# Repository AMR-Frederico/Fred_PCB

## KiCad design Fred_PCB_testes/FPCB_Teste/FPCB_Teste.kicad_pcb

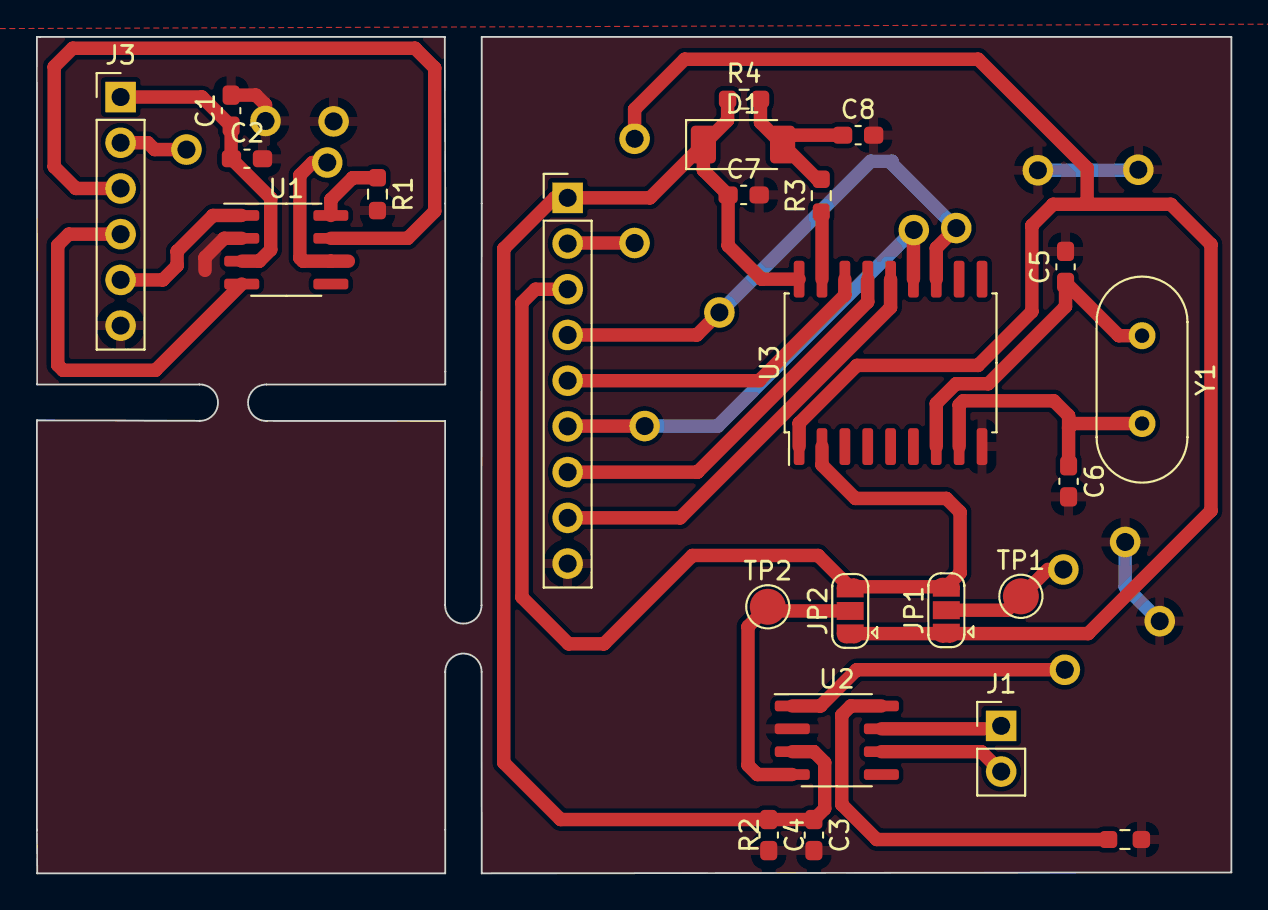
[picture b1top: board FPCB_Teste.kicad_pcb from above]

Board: 2 copper layers, 66.4 x 46.5 mm, 24 parts (0 on the bottom side), 23 nets.

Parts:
C1, C3, C7: 0,1uF; C_0603_1608Metric_Pad1.08x0.95mm_HandSolder
C2, C4: 2,2uF; C_0603_1608Metric_Pad1.08x0.95mm_HandSolder
C5, C6: 22pF; C_0603_1608Metric_Pad1.08x0.95mm_HandSolder
C8: C; C_0603_1608Metric_Pad1.08x0.95mm_HandSolder
D1: D; D_SOD-128
J1: Conn_01x02; PinHeader_1x02_P2.54mm_Vertical
J2: Conn_01x09; PinHeader_1x09_P2.54mm_Vertical
J3: Conn_01x06; PinHeader_1x06_P2.54mm_Vertical
JP1, JP2: SolderJumper_3_Open; SolderJumper-3_P1.3mm_Open_RoundedPad1.0x1.5mm
R1, R2: Rs; R_0603_1608Metric_Pad0.98x0.95mm_HandSolder
R3, R4: R; R_0603_1608Metric_Pad0.98x0.95mm_HandSolder
TP1, TP2: TestPoint; TestPoint_Pad_D2.0mm
U1, U2: SN65HVD230; SOIC-8_3.9x4.9mm_P1.27mm
U3: MCP2515-xSO; SOIC-18W_7.5x11.6mm_P1.27mm
Y1: Crystal; Crystal_HC49-4H_Vertical

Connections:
3,3v: C1.1, C2.1, C3.1, C4.1, C7.1, D1.1 (K), J2.1, J3.1, R4.1, U1.3 (VCC), U2.3 (VCC), U3.18 (VDD)
/MCP2515/GPIO9(MISO): J2.7, U3.15 (SO)
/MCP2515/GPIO10(MOSI): J2.8, U3.14 (SI)
/MCP2515/GPIO11(SCLK): J2.6, U3.13 (SCK)
/MCP2515/GPIO22: J2.5, U3.16 (~CS)
/MCP2515/GPIO26: J2.4, U3.12 (~INT)
/MCP2515/RXCAN: J2.3, JP1.3 (B), JP2.3 (B), U3.2 (RXCAN)
/MCP2515/TXCAN: J2.2, JP1.1 (A), JP2.1 (A), U3.1 (TXCAN)
/SN65HVD230/CANH: J3.3, U1.7 (CANH)
/SN65HVD230/CANL: J3.2, U1.6 (CANL)
/SN65HVD230/D: J3.5, U1.1 (D)
/SN65HVD230/R: J3.4, U1.4 (R)
/SN65HVD231_RASP/CANH: J1.1, U2.7 (CANH)
/SN65HVD231_RASP/CANL: J1.2, U2.6 (CANL)
/SN65HVD231_RASP/D: JP1.2 (C), TP1.1, U2.1 (D)
/SN65HVD231_RASP/R: JP2.2 (C), TP2.1, U2.4 (R)
GND: C1.2, C2.2, C3.2, C4.2, C5.2, C6.2, C7.2, C8.2, J2.9, J3.6, R1.2, R2.2, U1.2 (GND), U2.2 (GND), U3.9 (VSS)
unnamed: C8.1, D1.2 (A), R3.2, R4.2
unnamed: R1.1, U1.8 (Rs)
unnamed: R2.1, U2.8 (Rs)
unnamed: C6.1, U3.8 (OSC1), Y1.2
unnamed: C5.1, U3.7 (OSC2), Y1.1
unnamed: R3.1, U3.17 (~RESET)

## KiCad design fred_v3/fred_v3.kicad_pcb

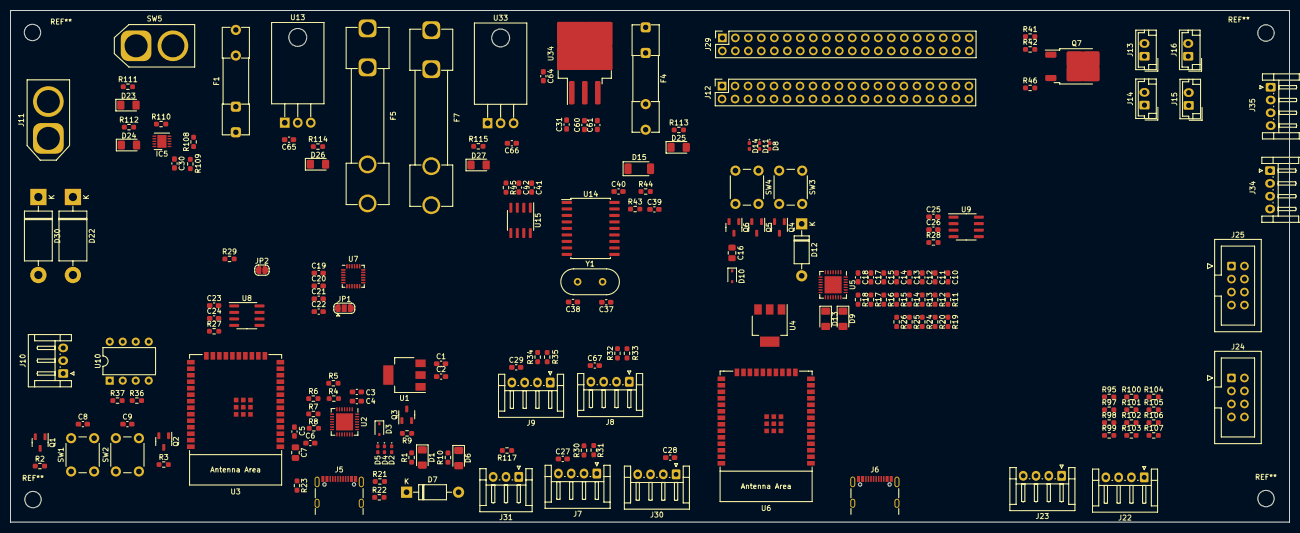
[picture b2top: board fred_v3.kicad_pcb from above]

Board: 2 copper layers, 250.0 x 100.0 mm, 185 parts (0 on the bottom side), 133 nets, no tracks yet.

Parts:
C1, C2, C10, C13, C64: 22uF; C_0603_1608Metric_Pad1.08x0.95mm_HandSolder
C3, C11: 4.7uF; C_0603_1608Metric_Pad1.08x0.95mm_HandSolder
C4, C5, C6, C8, C9, C12, C14, C15, C17, C18: 0.1uF; C_0603_1608Metric_Pad1.08x0.95mm_HandSolder
C7, C16: 22uF; C_0805_2012Metric_Pad1.18x1.45mm_HandSolder
C19: 2,2nF; C_0603_1608Metric_Pad1.08x0.95mm_HandSolder
C20: 2.2uF; C_0603_1608Metric_Pad1.08x0.95mm_HandSolder
C21, C23, C25, C40, C41, C65, C66: 0,1uF; C_0603_1608Metric_Pad1.08x0.95mm_HandSolder
C22: 10nF; C_0603_1608Metric_Pad1.08x0.95mm_HandSolder
C24, C26, C42, C60, C61: 2,2uF; C_0603_1608Metric_Pad1.08x0.95mm_HandSolder
C27, C28, C29, C67: 100nF; C_0603_1608Metric_Pad1.08x0.95mm_HandSolder
C30, C39: C; C_0603_1608Metric_Pad1.08x0.95mm_HandSolder
C31: 10uF; C_0603_1608Metric_Pad1.08x0.95mm_HandSolder
C37, C38: 22pF; C_0603_1608Metric_Pad1.08x0.95mm_HandSolder
D1, D6, D9, D13: LED; LED_1206_3216Metric_Pad1.42x1.75mm_HandSolder
D2, D4, D5, D8, D11, D14: GG0402055R042P; D_0402_1005Metric_Pad0.77x0.64mm_HandSolder
D3, D10: BAT760-7; D_SOD-323
D7, D12: 1N4007; D_DO-41_SOD81_P10.16mm_Horizontal
D15: D; D_SOD-128
D22, D30: DIODE 4AMP; D_DO-201AD_P15.24mm_Horizontal
D23: BLC; LED_1206_3216Metric_Pad1.42x1.75mm_HandSolder
D24: BLF; LED_1206_3216Metric_Pad1.42x1.75mm_HandSolder
D25: RSF; LED_1206_3216Metric_Pad1.42x1.75mm_HandSolder
D26: E1F; LED_1206_3216Metric_Pad1.42x1.75mm_HandSolder
D27: E2F; LED_1206_3216Metric_Pad1.42x1.75mm_HandSolder
F1: Fuse 6Amp; Fuseholder_Clip-5x20mm_Littelfuse_111_Inline_P20.00x5.00mm_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
F4: Fuse 4Amp; Fuseholder_Clip-5x20mm_Littelfuse_111_Inline_P20.00x5.00mm_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
F5, F7: Fuse 1Amp; Fuseholder_Clip-6.3x32mm_Littelfuse_102_Inline_P34.21x7.62m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
IC5: PAC1921-1-AIA-TR; WDFN-10-1EP_3x3mm_P0.5mm_EP1.8x2.5mm
J5, J6: USB_C_Receptacle_USB2.0; USB_C_Receptacle_GCT_USB4105-xx-A_16P_TopMnt_Horizontal
J7, J8, J9, J22, J23, J30, J34, J35: Conn_01x04; JST_EH_S4B-EH_1x04_P2.50mm_Horizontal
J10, J31: Conn_01x03; JST_EH_S3B-EH_1x03_P2.50mm_Horizontal
J11: Conn_01x02; AMASS_XT60-M_1x02_P7.20mm_Vertical
J12, J29: Conn_02x20_Odd_Even; PinSocket_2x20_P2.54mm_Vertical
J13: FAN1; JST_EH_B2B-EH-A_1x02_P2.50mm_Vertical
J14: FAN2; JST_EH_B2B-EH-A_1x02_P2.50mm_Vertical
J15: FAN3; JST_EH_B2B-EH-A_1x02_P2.50mm_Vertical
J16: FAN4; JST_EH_B2B-EH-A_1x02_P2.50mm_Vertical
J24, J25: Conn_02x04_Odd_Even; IDC-Header_2x04_P2.54mm_Vertical
JP1: SolderJumper_3_Open; SolderJumper-3_P1.3mm_Open_RoundedPad1.0x1.5mm
JP2: SolderJumper_2_Open; SolderJumper-2_P1.3mm_Open_RoundedPad1.0x1.5mm
Q1, Q2, Q5, Q6: SS8050-G; SOT-23-3
Q3, Q4: Q_PMOS_GSD; SOT-23-3
Q7: NMOS; TO-252-2
R1, R6, R15, R18: 2k; R_0603_1608Metric_Pad0.98x0.95mm_HandSolder
R2, R3, R7, R8, R13, R14, R19, R20, R46, R98, R101, R104, R107: 10k; R_0603_1608Metric_Pad0.98x0.95mm_HandSolder
R4, R16: 22.1k; R_0603_1608Metric_Pad0.98x0.95mm_HandSolder
R5, R17: 47.5k; R_0603_1608Metric_Pad0.98x0.95mm_HandSolder
R9, R11: 1K; R_0603_1608Metric_Pad0.98x0.95mm_HandSolder
R10, R12: 1k; R_0603_1608Metric_Pad0.98x0.95mm_HandSolder
R21, R24, R41, R42, R43, R44, R109, R110: R; R_0603_1608Metric_Pad0.98x0.95mm_HandSolder
R22, R23, R25, R26: 5,11k; R_0603_1608Metric_Pad0.98x0.95mm_HandSolder
R27, R28, R45: Rs; R_0603_1608Metric_Pad0.98x0.95mm_HandSolder
R29: 120; R_0603_1608Metric_Pad0.98x0.95mm_HandSolder
R30, R31, R32, R33, R34, R35: 10K; R_0603_1608Metric_Pad0.98x0.95mm_HandSolder
R36: 3,5k; R_0603_1608Metric_Pad0.98x0.95mm_HandSolder
R37: 6,5k; R_0603_1608Metric_Pad0.98x0.95mm_HandSolder
R95, R99, R102, R105: 4,7k; R_0603_1608Metric_Pad0.98x0.95mm_HandSolder
R97, R100, R103, R106: 2,2k; R_0603_1608Metric_Pad0.98x0.95mm_HandSolder
R108: R_Shunt; R_0603_1608Metric_Pad0.98x0.95mm_HandSolder
R111, R112, R113, R114, R115: 330; R_0603_1608Metric_Pad0.98x0.95mm_HandSolder
R117: Pull_Up Hall (Pode não ser necessário); R_0603_1608Metric_Pad0.98x0.95mm_HandSolder
SW1, SW2, SW3, SW4: SW_Push; SW_PUSH_6mm
SW5: SW_DIP_x01; AMASS_XT60-M_1x02_P7.20mm_Vertical
U1, U4: AMS1117-3.3; SOT-223-3_TabPin2
U2, U5: CP2102N-Axx-xQFN28; QFN-28-1EP_5x5mm_P0.5mm_EP3.35x3.35mm
U3, U6: ESP32-WROOM-E; ESP32-WROOM-32E
U7: MPU-6050; InvenSense_QFN-24_4x4mm_P0.5mm
U8, U9, U15: SN65HVD230; SOIC-8_3.9x4.9mm_P1.27mm
U10: AD8001AN; DIP-8_W7.62mm
U13, U33: L7805; TO-220-3_Horizontal_TabDown
U14: MCP2515-xSO; SOIC-18W_7.5x11.6mm_P1.27mm
U34: AZ1084-5.0; TO-263-3_TabPin2
Y1: Crystal; Crystal_HC49-4H_Vertical

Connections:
3,3V: C2.1, C3.1, C4.1, C6.1, C7.1, C20.1, C22.2, C23.1, C24.1, JP1.3 (B), R6.1, R8.1, U1.2 (VO), U2.6 (VDD), U2.7 (VREGIN), U3.2 (3V3), U7.8 (VLOGIC), U7.13 (VDD), U8.3 (VCC)
3,3v: C25.1, C26.1, C40.1, C41.1, C42.1, D15.1 (K), J12.1, J12.17, J29.1, J29.17, J34.4, J35.4, R41.1, R42.1, R44.1, R109.1, U9.3 (VCC), U14.18 (VDD), U15.3 (VCC)
3.3V: C11.1, C12.1, C13.1, C15.1, C16.1, R18.1, R20.1, U4.2 (VO), U5.6 (VDD), U5.7 (VREGIN), U6.2 (3V3)
5V: F4.2, IC5.7 (RESERVED), J12.2, J12.4, J29.2, J29.4, R113.1
5V_1: C65.1, F5.1, U13.3 (OUT)
5V_2: C66.1, F7.1, U33.3 (OUT)
5V_USB: C1.1, C10.1, D3.1 (K), D7.1 (K), D10.1 (K), D12.1 (K), Q3.1 (G), Q4.1 (G), R1.1, R4.1, R9.2, R11.2, R15.1, R16.1, U1.3 (VI), U4.3 (VI)
12V_IN: F1.2, SW5.2
/Lógica/CANH: R29.1, U8.7 (CANH), U9.7 (CANH), U15.7 (CANH)
/Lógica/CANL: JP2.1 (A), U8.6 (CANL), U9.6 (CANL), U15.6 (CANL)
/Lógica/LED_LVL_SHIFTER/EXT_5V: J10.2, R37.1, U10.7 (V+)
/Lógica/LED_LVL_SHIFTER/LED_OUT: J10.1, U10.6
A_LEFT: J22.3, R95.1, R97.1
A_RIGHT: J23.3, R102.1, R103.1
B_LEFT: J22.4, R99.1, R100.1
B_RIGHT: J23.4, R105.1, R106.1
Current_Sense1: J24.2, J25.2, U6.24 (ADC2_CH2/GPIO2)
Current_Sense2: J24.4, J25.4, U6.26 (ADC2_CH0/GPIO4)
D+: D5.2 (A2), D14.2 (A2), J5.A6 (D+), J5.B6 (D+), J6.A6 (D+), J6.B6 (D+), U2.4 (D+), U5.4 (D+)
D-: D4.2 (A2), D11.2 (A2), J5.A7 (D-), J5.B7 (D-), J6.A7 (D-), J6.B7 (D-), U2.5 (D-), U5.5 (D-)
DTR: Q2.2 (C), Q6.2 (C), R2.1, R13.1, U2.28 (~DTR), U5.28 (~DTR)
ECHO1: J7.2, R30.1
ECHO2: J8.2, R32.1
ECHO3: J9.2, R34.1
EN: C5.1, C8.2, C14.1, C17.2, Q1.2 (C), Q5.2 (C), R8.2, R20.2, SW1.2, SW3.2, U3.3 (EN/CHIP_PU), U6.3 (EN/CHIP_PU)
EXT_5V: C27.1, C28.1, C29.1, C67.1, F5.2, F7.2, J7.4, J8.4, J9.4, J22.1, J23.1, J30.1, J31.1, Q3.3 (D), Q4.3 (D), R95.2, R99.2, R102.2, R105.2, R114.1, R115.1, R117.1
GND: C1.2, C2.2, C3.2, C4.2, C5.2, C6.2, C7.2, C8.1, C9.1, C10.2, C11.2, C12.2, C13.2, C14.2, C15.2, C16.2, C17.1, C18.1, C19.2, C20.2, C21.2, C22.1, C23.2, C24.2, C25.2, C26.2, C27.2, C28.2, C29.2, C30.2, C31.2, C37.2, C38.2, C39.2, C40.2, C41.2, C42.2, C60.2, C61.2, C64.2, C65.2, C66.2, C67.2, D1.1 (K), D2.1 (A1), D4.1 (A1), D5.1 (A1), D6.1 (K), D8.1 (A1), D9.1 (K), D11.1 (A1), D13.1 (K), D14.1 (A1), D22.2 (A), D23.1 (K), D24.1 (K), D25.1 (K), D26.1 (K), D27.1 (K), D30.2 (A), IC5.5 (GND), IC5.11 (EP), J5.A1 (GND), J5.A12 (GND), J5.B1 (GND), J5.B12 (GND), J6.A1 (GND), J6.A12 (GND), J6.B1 (GND), J6.B12 (GND), J7.1, J8.1, J9.1, J10.3, J12.6, J12.9, J12.14, J12.20, J12.25, J12.30, J12.34, J12.39, J13.2, J14.2, J15.2, J16.2, J22.2, J23.2, J29.6, J29.9, J29.14, J29.20, J29.25, J29.30, J29.34, J29.39, J30.2, J31.2, J34.3, J35.3, JP1.1 (A), R5.2, R7.2, R9.1, R11.1, R17.2, R19.2, R21.2, R22.2, R23.2, R24.2, R25.2, R26.2, R27.2, R28.2, R31.1, R33.1, R35.1, R36.2, R45.2, R46.1, R98.1, R101.1, R104.1, R107.1, R110.2, SW1.1, SW2.1, SW3.1, SW4.1, U1.1 (GND), U2.3 (GND), U2.29 (GND), U3.1 (GND), U3.15 (GND), U3.38 (GND), U3.39 (GND_THERMAL), U4.1 (GND), U5.3 (GND), U5.29 (GND), U6.1 (GND), U6.15 (GND), U6.38 (GND), U6.39 (GND_THERMAL), U7.1 (CLKIN), U7.11 (FSYNC), U7.18 (GND), U8.2 (GND), U9.2 (GND), U10.4 (V-), U13.2 (GND), U14.9 (VSS), U15.2 (GND), U33.2 (GND), U34.1 (GND)
GPIO0(ID_SD): J12.27, J29.27
GPIO1(ID_SC): J12.28, J29.28
GPIO2(SDA): IC5.9 (SM_DATA), J12.3, J29.3, J34.2, J35.2, R42.2
GPIO3(SCL): IC5.10 (SM_CLK), J12.5, J29.5, J34.1, J35.1, R41.2
GPIO4(GPCLK0): J12.7, J29.7
GPIO5: J12.29, J29.29
GPIO6: IC5.8 (~READ/INT), J12.31, J29.31
GPIO7(CE1): J12.26, J29.26
GPIO8(CE0): J12.24, J29.24
GPIO9(MISO): J12.21, J29.21, U14.15 (SO)
GPIO10(MOSI): J12.19, J29.19, U14.14 (SI)
GPIO11(SCLK): J12.23, J29.23, U14.13 (SCK)
GPIO12(PWM0): J12.32, J29.32, Q7.2 (G), R46.2
GPIO13(PWM1): J12.33, J29.33
GPIO14(TXD): J12.8, J29.8
GPIO15(RXD): J12.10, J29.10
GPIO16: J12.36, J29.36
GPIO17: J12.11, J29.11
GPIO18(PCM_CLK): J12.12, J29.12
GPIO19(PCM_FS): J12.35, J29.35
GPIO20(PCM_DIN): J12.38, J29.38
GPIO21(PCM_DOUT): J12.40, J29.40
GPIO22: J12.15, J29.15, U14.16 (~CS)
GPIO23: J12.16, J29.16
GPIO24: J12.18, J29.18
GPIO25: J12.22, J29.22
GPIO26: J12.37, J29.37, U14.12 (~INT)
GPIO27: J12.13, J29.13
INA_M1_FRONT: J24.1, J25.1, U6.8 (32K_XP/GPIO32/ADC1_CH4)
INA_M2_FRONT: J24.7, J25.7, U6.28 (GPIO17)
INB_M1_FRONT: J24.3, J25.3, U6.29 (GPIO5)
INB_M2_FRONT: J24.6, J25.6, U6.30 (GPIO18)
INT: U3.30 (GPIO18), U7.12 (INT)
IO0: C9.2, C18.2, Q2.3 (E), Q6.3 (E), SW2.2, SW4.2, U3.25 (GPIO0/BOOT/ADC2_CH1), U6.25 (GPIO0/BOOT/ADC2_CH1)
IO5: U3.29 (GPIO5), U10.3 (+)
IO12: J9.3, U3.14 (MTDI/GPIO12/ADC2_CH5)
IO13: U3.16 (MTCK/GPIO13/ADC2_CH4), U6.16 (MTCK/GPIO13/ADC2_CH4)
IO14: U3.13 (MTMS/GPIO14/ADC2_CH6), U6.13 (MTMS/GPIO14/ADC2_CH6)
IO16: U3.27 (GPIO16), U8.4 (R), U9.4 (R)
IO17: U3.28 (GPIO17), U8.1 (D), U9.1 (D)
IO21: J30.4, U3.33 (GPIO21), U7.24 (SDA)
IO25: J7.3, U3.10 (DAC_1/ADC2_CH8/GPIO25)
IO27: J8.3, U3.12 (ADC2_CH7/GPIO27)
IO32: R34.2, R35.2, R97.2, R98.2, U3.8 (32K_XP/GPIO32/ADC1_CH4)
IO33: R100.2, R101.2, U3.9 (32K_XN/GPIO33/ADC1_CH5), U6.9 (32K_XN/GPIO33/ADC1_CH5)
IO34: R32.2, R33.2, R103.2, R104.2, U3.6 (GPIO34/ADC1_CH6), U6.6 (GPIO34/ADC1_CH6)
IO35: R106.2, R107.2, U3.7 (GPIO35/ADC1_CH7), U6.7 (GPIO35/ADC1_CH7)
IO36: R30.2, R31.2, U3.4 (SENSOR_VP/GPIO36/ADC1_CH0), U6.4 (SENSOR_VP/GPIO36/ADC1_CH0)
IO39: J31.3, R117.2, U3.5 (SENSOR_VN/GPIO39/ADC1_CH3), U6.5 (SENSOR_VN/GPIO39/ADC1_CH3)
unnamed: D1.2 (A), R1.2
unnamed: D6.2 (A), R10.2
unnamed: D7.2 (A), Q3.2 (S), R10.1
unnamed: D9.2 (A), R12.2
unnamed: D12.2 (A), Q4.2 (S), R12.1
unnamed: D13.2 (A), R15.2
unnamed: C39.1, D15.2 (A), R43.2, R44.2
unnamed: D22.1 (K), D30.1 (K), J11.1
unnamed: D23.2 (A), R111.2
unnamed: D24.2 (A), R112.2
unnamed: D25.2 (A), R113.2
unnamed: D26.2 (A), R114.2
unnamed: D27.2 (A), R115.2
unnamed: IC5.6 (ADDR_SEL), R110.1
unnamed: F1.1, IC5.2 (SENSE+), R108.1
unnamed: C30.1, IC5.1 (VDD), R109.2
unnamed: J5.A5 (CC1), R23.1
unnamed: J5.B5 (CC2), R22.1
unnamed: J5.S1 (SHIELD), R21.1
unnamed: J6.A5 (CC1), R26.1
unnamed: J6.B5 (CC2), R25.1
unnamed: J6.S1 (SHIELD), R24.1
unnamed: J11.2, R111.1, SW5.1
unnamed: J13.1, J14.1, J15.1, J16.1, Q7.3 (S)
unnamed: JP1.2 (C), U7.9 (AD0)
unnamed: JP2.2 (B), R29.2
unnamed: Q1.1 (B), R2.2
unnamed: Q2.1 (B), R3.2
unnamed: Q5.1 (B), R13.2
unnamed: Q6.1 (B), R14.2
unnamed: R6.2, U2.9 (~RST)
unnamed: R7.1, U2.11 (~SUSPEND)
unnamed: R18.2, U5.9 (~RST)
unnamed: R19.1, U5.11 (~SUSPEND)
unnamed: C19.1, U7.20 (CPOUT)
unnamed: C21.1, U7.10 (REGOUT)
unnamed: R27.1, U8.8 (Rs)
unnamed: R28.1, U9.8 (Rs)
unnamed: R36.1, R37.2, U10.2 (-)
unnamed: C37.1, U14.8 (OSC1), Y1.2
unnamed: C38.1, U14.7 (OSC2), Y1.1
unnamed: R43.1, U14.17 (~RESET)
unnamed: R45.1, U15.8 (Rs)
unnamed: C64.1, F4.1, U34.2 (VO)
PWM_M1_FRONT: J24.5, J25.5, U6.27 (GPIO16)
PWM_M2_FRONT: J24.8, J25.8, U6.31 (GPIO19)
RTS: Q1.3 (E), Q5.3 (E), R3.1, R14.1, U2.24 (~RTS), U5.24 (~RTS)
RXCAN: U14.2 (RXCAN), U15.4 (R)
RXD: U2.25 (RXD), U5.25 (RXD)
RXD0: U3.35 (U0TXD/GPIO1), U6.35 (U0TXD/GPIO1)
SCL: J30.3, U3.36 (GPIO22), U7.23 (SCL)
SENSED_12V: C31.1, C60.1, C61.1, IC5.3 (SENSE-), Q7.1 (D), R108.2, R112.1, U13.1 (IN), U33.1 (IN), U34.3 (VI)
TXCAN: U14.1 (TXCAN), U15.1 (D)
TXD: U2.26 (TXD), U5.26 (TXD)
TXD0: U3.34 (U0RXD/GPIO3), U6.34 (U0RXD/GPIO3)
VBUS: D2.2 (A2), D3.2 (A), D8.2 (A2), D10.2 (A), J5.A4 (VBUS), J5.A9 (VBUS), J5.B4 (VBUS), J5.B9 (VBUS), J6.A4 (VBUS), J6.A9 (VBUS), J6.B4 (VBUS), J6.B9 (VBUS)
VBUS_CP210: R4.2, R5.1, R16.2, R17.1, U2.8 (VBUS), U5.8 (VBUS)

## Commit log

2024-04-04 Fred PCBs para prototipagem
